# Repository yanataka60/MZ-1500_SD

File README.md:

# MZ-1500にSD-CARDからのアプリケーション起動、ロード、セーブ機能

MZ-1500でSD-CARDからのアプリケーション起動、BASICなどのアプリケーションからSD-CARDへのロード、セーブを実現するものです。

#### 2024.8.8 BASIC MZ-5Z001でSD対応パッチ更新しました。今のところ、LOAD、SAVEに問題は発生していません。
#### ~~2024.8.6 BASIC MZ-5Z001でSDからのLOAD実行した後に別プログラムをLOADしようとすると高確率で暴走してしまうようです。原因調査中ですので使用にはご注意ください。~~
#### 2024.8.5 BASIC MZ-5Z001でSDからのLOAD、SAVEに対応しました。
#### ~~MZ-1500でSD-CARDからのアプリケーション起動、BASICなどのアプリケーションからSD-CARDへのロード、セーブを実現するものですが、現在は標準BASIC MZ-5Z001もBASICプログラムのLOAD、SAVEに対応できていませんので機械語ゲームの起動等限定的な利用になります。~~

　MZ-1500にはMZ-1R12が装備されているとS-RAMに保存されているプログラムから起動する機能がありますが、疑似的にMZ-1R12のふりをすることでMZ-1500_SDに搭載したROMからSD-CARDからアプリケーションを起動させる機能を持たせたMONITORプログラムを起動させます。

　SD対応MONITORからはFD又はFDLコマンドでSDからアプリケーションをLOAD実行ができます。

　SD対応MONITORは本体ROMの1Z-009BをRAMにコピーしてうえでSD対応のプログラムを付加しています。

　LOAD実行範囲は、0000h～CFFFhです。アプリケーション、ゲームを起動させるにはほぼ問題ないと思います。

　ただし、多段ロード、QDソフトには対応していません。

　なお、アプリケーション中でのSD-CARDとのロード、セーブについては、MZ-80Kシリーズ、MZ-1200、MZ-700、MZ-1500のすべてのアプリケーションごとにSD-CARD対応化を行う必要があります。

　現在、アプリケーション中でのSD-CARDとのLOAD、SAVEに対応できているものは以下のとおりです。

|アプリケーション名|備考|
| ------------ | ------------ |
|BASIC MZ-5Z001||
|MZ-700用SBasic 1Z-007B||
|ROPOKO v1.2.2||
|ROPOKO体験版||
|ROPOKO80K v1.1.2||

　なお、Arduino、ROMへ書き込むための機器が別途必要となります。

### (2026.8.15追記)多段ロードに対応するためArduinoプログラム及び1Z-009B_SD_Launcher.binを更新しました。

### 多段ロードの詳細についてはMZ-80K_SDの「多段ロード対応」を参照してください。

　多段ロード対応:https://github.com/yanataka60/MZ80K_SD#%E5%A4%9A%E6%AE%B5%E3%83%AD%E3%83%BC%E3%83%89%E5%AF%BE%E5%BF%9C2026813

#### 　ただし、SDアクセスルーチンがROM上にあるMZ-80K_SD、MZ-700_SDとは違いMZ-1500_SDはRAM上にあるため、１段目のプログラムのロード範囲がC100h以降であるとSDアクセスルーチンを破壊してしまい、多段ロードが機能しません。

　ArduinoプログラムはMZ-80K_SD用に更新したものがそのまま使えます。

## 回路図
　KiCadフォルダ内のMZ-1500_SD.pdfを参照してください。

[回路図](https://github.com/yanataka60/MZ-1500_SD/blob/main/KiCad/MZ-1500_SD.pdf)

|番号|品名|数量|備考|
| ------------ | ------------ | ------------ | ------------ |
||J2、J3のいずれか|||
|J2|Micro_SD_Card_Kit|1|秋月電子通商 AE-microSD-LLCNV (注1)|
|J3|MicroSD Card Adapter|1|Arduino等に使われる5V電源に対応したもの(注3)|
|U1,U2|74LS04|2||
|U3,U4|74LS30|2||
|U5|74LS10|1||
|U6|74LS14|1||
|U7|8255|1||
|U8|Arduino_Pro_Mini_5V|1|Atmega328版を使用 168版は不可。(注2)|
|U9-U12|74LS193|4||
|U13|27256/29C256/27512/27C512相当品|1|27256/29C256を使うときは、S1を5V側にして使うこと。28C256はピン配置が違うので使えません。|
|U14|74LS245|1||
|C1,C2,C4-C14|積層セラミックコンデンサ 0.1uF|13||
|C3|電解コンデンサ 16v100uF|1||
|C15|積層セラミックコンデンサ 220pF|1||
|R1|カーボン抵抗 100Ω|1||
|S1|3Pスライドスイッチ|1|秋月電子通商 SS12D01G4など|
||ピンヘッダ|2Pin分|Arduino_Pro_MiniにはA4、A5用のピンヘッダが付いていないため別途調達が必要です 秋月電子通商 PH-1x40SGなど|
||ピンソケット(任意)|26Pin分|Arduino_Pro_Miniを取り外し可能としたい場合に調達します 秋月電子通商 FHU-1x42SGなど|

　　　注1)秋月電子通商　AE-microSD-LLCNVのJ1ジャンパはショートしてください。

　　　注2)Arduino Pro MiniはA4、A5ピンも使っています。

　　　注3)MicroSD Card Adapterを使う場合

　　　　　J3に取り付けます。

MicroSD Card Adapterについているピンヘッダを除去してハンダ付けするのが一番確実ですが、J3の穴にMicroSD Card Adapterをぴったりと押しつけ、裏から多めにハンダを流し込むことでハンダ付けをする方法もあります。なお、この方法の時にはしっかりハンダ付けが出来たかテスターで導通を確認しておいた方が安心です。

ハンダ付けに自信のない方はJ2の秋月電子通商　AE-microSD-LLCNVをお使いください。AE-microSD-LLCNVならパワーLED、アクセスLEDが付いています。

## ROMへの書込み
　Z80フォルダの「1Z-009B_Launcher」フォルダ内の1Z-009B_SD_Launcher.binをROMライター(TL866II Plus等)を使って27C256に書き込んでください。

　27C512を使えば二つのバイナリファイルを切り替えて使うような使い方ができます。このとき、一つのバイナリファイルは32KByte、二つ合わせて64KByteにして書き込んでください。

　もうひとつのLauncherとして「Oh!MZ別冊 ADVANCED MZ-700」に掲載されたMZ-80K/CコンパチモニタFN-700をベースとしたFN-700_1500SD_Launcherを作成しました。

### FN-700_1500SD_Launcher.bin作成手順
　1)「Oh!MZ別冊 ADVANCED MZ-700」掲載のMZ-80K/CコンパチモニタFN-700のMZTファイルを用意します。

　2)MZTファイルのヘッダ128Byte分は不要ですのでバイナリエディタで削除します。

　3)先頭の16Byteも不要ですので削除し、C3 4A 00から始まる4096Byteのファイルとします。

　4)以下のアドレスを修正します。

|ADDRESS|修正前|修正後|
| ------------ | ------------ | ------------ |
|0179|F0|C1|
|0437|D5 C5 E5|C3 04 C1|
|0476|D5 C5 E5|C3 07 C1|
|04D9|D5 C5 E5|C3 0A C1|
|04F9|D5 C5 E5|C3 0D C1|
|0589|D5 C5 E5|C3 10 C1|

　5)Z80フォルダの「FN-700_Launcher」フォルダ内のFN-700_1500SD.binを先程加工したFN-700の後ろに連結します。6430Byteのファイルになります。

　6)先頭に9Byteのヘッダ「00 00 00 12 00 22 00 00 00」を付加します。6439Byteのファイルになります。FN-700_1500SD_DATA.binなど適当なファイル名を付けて保存します。

　7)Z80フォルダの「FN-700_Launcher」フォルダ内の1Z-1R12_Header.exeを実行し、先程作成したFN-700_1500SD_DATA.binをドラッグ＆ドロップします。

　8)1Z-1R12_Header.exeを起動したフォルダにチェックサムを正しく計算したMZ1500SD.ROMが作成されます。6574Byteのファイルになっているはずです。

　9)MZ1500SD.ROM(FN-700_1500SD_Launcher.bin)をROMライター(TL866II Plus等)を使ってROMに書き込んでください。

　または、5)で出来たファイルに以下のヘッダを付けてMZTファイルとして保存すれば1Z-009B_Launcherから実行することもできます。

[0000] 01 46 4E 2D 37 30 30 20 31 35 30 30 53 44 0D 0D

[0010] 0D 0D 1E 19 00 12 00 22 00 00 00 00 00 00 00 00

[0020] 00 00 00 00 00 00 00 00 00 00 00 00 00 00 00 00

[0030] 00 00 00 00 00 00 00 00 00 00 00 00 00 00 00 00

[0040] 00 00 00 00 00 00 00 00 00 00 00 00 00 00 00 00

[0050] 00 00 00 00 00 00 00 00 00 00 00 00 00 00 00 00

[0060] 00 00 00 00 00 00 00 00 00 00 00 00 00 00 00 00

[0070] 00 00 00 00 00 00 00 00 00 00 00 00 00 00 00 00

## Arduinoプログラム

　MZ-80K_SDと全く同じものを使用しています。

https://github.com/yanataka60/MZ80K_SD/tree/main/Arduino/MZ-80K_SD

　MZ-80K_SDでソケットを使用して差込式にしているのであればそのままMZ-1500_SDに差して使えます。

　Arduino IDEを使ってMZ-80Kリポジトリ Arduinoフォルダ内のMZ-80K_SD.inoを書き込みます。

　SdFatライブラリを使用しているのでArduino IDEメニューのライブラリの管理からライブラリマネージャを立ち上げて「SdFat」をインストールしてください。

　「SdFat」で検索すれば見つかります。「SdFat」と「SdFat - Adafruit Fork」が見つかりますが「SdFat」のほうを使っています。

注)Arduinoを基板に直付けしている場合、Arduinoプログラムを書き込むときは、MZ-15000本体とは接続を外し、74LS04を外したうえで書き込んでください。

## 接続
　拡張スロットに差し込んで使います。

　なお、拡張スロットから引き抜くときに引き抜きやすいよう基板両サイドと中央に穴を開けてあります。

　穴にドライバー等を引っ掛けて押し出すようにすれば引き抜きやすいと思います。

## SD-CARD
　出来れば8GB以下のSDカードを用意してください。

　ArduinoのSdFatライブラリは、SD規格(最大2GB)、SDHC規格(2GB～32GB)に対応していますが、SDXC規格(32GB～2TB)には対応していません。

　また、SDHC規格のSDカードであっても32GB、16GBは相性により動作しないものがあるようです。

　FAT16又はFAT32が認識できます。NTFSは認識できません。

　ルートに置かれたMZTファイルのみ認識できます。(MZT以外のファイル、フォルダも表示されますがLOAD実行の対象になりません)

　ファイル名は「.MZT」を除いて32文字まで、ただし半角カタカナ、及び一部の記号はArduinoが認識しないので使えません。パソコンでファイル名を付けるときはアルファベット、数字および空白でファイル名をつけてください。

## 操作方法
　ROM起動させた場合にMONITORコマンド入力待ちから以下のコマンドが拡張されます。

　以下、SD-CARD内のファイルに付けられるファイル名をDOSファイル名、MZT形式ファイルのインフォメーションブロック内ファイル名をIBFファイル名とします。

### FD[CR]
　FDのみでDOSファイル名「0000.MZT」がLOAD及び実行されます。

　「0000.MZT」は、パソコンでBASIC等をリネームコピーして作成してください。

　LOAD実行可能範囲は0000h～CFFFhです。

### FD　DOSファイル名[CR]
　DOSファイル名で指定したバイナリファイルをLOADして実行します。

　「.MZT」は省略可能です。

　LOAD実行可能範囲は0000h～CFFFhです。

例)

FD　TEST[CR]

### FDL[CR]
　SD-CARDルートディレクトリにあるファイルの一覧を表示します。20件表示したところで指示待ちになるので打ち切るならSHIFT+BREAK又は↑を入力すると打ち切られ、Bキーで前の20件に戻ります。それ以外のキーで次の20件を表示します。

　行頭に「*FD」を付加して表示してあるので実行したいファイルにカーソルキーを合わせて[CR]キーを押すだけでLOAD、実行が可能です。

　表示される順番は、登録順となりファイル名アルファベッド順などのソートした順で表示することはできません。

　LOAD実行可能範囲は0000h～CFFFhです。

### FDL　x[CR]
ファイル名がxで始まるファイルの一覧を表示します。20件表示したところで指示待ちになるので打ち切るならSHIFT+BREAK又は↑を入力すると打ち切られ、Bキーで前の20件に戻ります。それ以外のキーで次の20件を表示します。

xはMZのキーボードから入力可能な32文字までの文字列です。(数字、記号、アルファベット)

　LOAD実行可能範囲は0000h～CFFFhです。

例)

FDL S[CR]

FDL SP[CR]

FDL BASIC S[CR]

### FDA　DOSファイル名[CR]
　DOSファイル名で指定したファイルを「0000.MZT」という名前でリネームコピーします。

　FDLコマンドで表示されたファイル名をカーソルで選択し、行頭の「*FD」に「A」だけ付加して[CR]キーを押せば簡単です。

### FDS　SAVE開始アドレス　SAVE終了アドレス　実行開始アドレス　DOSファイル名[CR]
　SAVE開始アドレスからSAVE終了アドレスまでをDOSファイル名でSAVEします。

　SAVE開始アドレス、SAVE終了アドレス、実行開始アドレスは16進数4桁で指定します。DOSファイル名の「.MZT」は省略可能です。

例)

FDS　1200　2FFF　1200　TEST[CR]

### FDC　DOSファイル名[CR]
　DOSファイル名で指定したファイルをコピーします。

　FDLコマンドで表示されたファイル名をカーソルで選択し、行頭の「*FD」に「C」だけ付加して[CR]キーを押せば簡単です。

　DOSファイル名を入力し、[CR]キーを押すと「NEW NAME:」と聞いてくるので新しいDOSファイル名を入力して[CR]キーを押します。

　新しいDOSファイル名に既にあるDOSファイル名を指定するとコピーせずに中断します。

例)

FDC　TEST[CR]

NEW NAME:TEST2[CR]

### FDR　DOSファイル名[CR]
　DOSファイル名で指定したファイルをリネームします。

　FDLコマンドで表示されたファイル名をカーソルで選択し、行頭の「*FD」に「R」だけ付加して[CR]キーを押せば簡単です。

　DOSファイル名を入力し、[CR]キーを押すと「NEW NAME:」と聞いてくるので新しいDOSファイル名を入力して[CR]キーを押します。

　新しいDOSファイル名に既にあるDOSファイル名を指定するとリネームせずに中断します。

例)

FDR　TEST[CR]

NEW NAME:TEST2[CR]

### FDD　DOSファイル名[CR]
　DOSファイル名で指定したファイルを削除します。

　FDLコマンドで表示されたファイル名をカーソルで選択し、行頭の「*FD」に「D」だけ付加して[CR]キーを押せば簡単です。

　DOSファイル名を入力し、[CR]キーを押すと「FILE DELETE?(Y:OK ELSE:CANSEL)」と聞いてくるのでYを押せば削除されます。Y以外のキーを押すとキャンセルとなります。

### FDP　DOSファイル名[CR]
　DOSファイル名で指定したファイルの内容をDUMPします。

　FDLコマンドで表示されたファイル名をカーソルで選択し、行頭の「*FD」に「P」だけ付加して[CR]キーを押せば簡単です。

　DOSファイル名を入力し、[CR]キーを押すとファイルの内容を128Byteを一画面として表示します。

　一画面表示したところで「NEXT:ANY BACK:B BREAK:SHIFT+BREAK」と表示して指示待ちとなるのでBで前の128Byteを表示、SHIFT+BREAKで中止、それ以外のキーで次の128Byteの表示となります。

　ファイルサイズが128Byteで割り切れない場合には最後のページは128Byteに揃うまで00Hで埋められます。

　ファイル内容を書き換えることはできません。

### FDM　開始アドレス[CR]
　開始アドレスからMZ-80Kのメモリ内容を128Byteを一画面として表示します。

　一画面表示したところで「NEXT:ANY BACK:B BREAK:SHIFT+BREAK」と表示して指示待ちとなるのでBで前の128Byteを表示、SHIFT+BREAKで中止、それ以外のキーで次の128Byteの表示となります。

　一画面表示している途中でもSHIFT+BREAKでいつでも中止できます。

### FDW　開始アドレス　1Byte(16進2桁)データ[CR]
　開始アドレスから16進2桁データをMZ-80Kのメモリに書き込みます。

　開始アドレスに続けて16進2桁で書き込むデータを記述し[CR]キーを押します。データの区切りの空白は無視しますのであってもなくても構いません。

　16進2桁のByteデータは一行に収まる範囲なら何Byte分を続けても構いません。

　一行入力して[CR]キーを押すとデータが書き込まれ、次のアドレスが表示されるので続けてデータを入力していけます。

　また、アドレスを修正すれば戻って修正や離れたアドレスにデータを書き込むことも可能です。

　データの書き込みを止めるときは表示されたアドレスにデータを書かずに[CR]キーを押します。

　16進数以外を入力して[CR]キーを押した場合には16進数以外を入力した直前までの有効なデータを書き込み次のアドレスを表示します。

例)

*FDW　1200　01　02　03　04　05　06　07　08[CR]

*FDW　1200　0102030405060708[CR]

*FDW　1200[CR]　(止めるとき)

*FDW　1200　12　34　5/[CR]　(12　34まで書き込まれます)

## アプリケーションからのLOAD、SAVE
　MZ-1500はE800h～FFFFhにROMが置かれており、MZ-80Kシリーズ、MZ-1200、MZ-700のように特定のアドレス(F000h等)にSDアクセスルーチンを格納したROMを置くことが出来ないため、SDへのLOAD、SAVEはアプリケーション個々にSDアクセスルーチンをどこに置くか検討が必要になります。

　また、文字列入力等モニタルーチンを使っている箇所があるのでSP-1002、MZ-1Z009Bではない独自MONITOR上で動くアプリケーションはMONITORの解析も必要です。

　「Oh!MZ別冊 ADVANCED MZ-700」に掲載されたMZ-80K/CコンパチモニタFN-700を使えばMZ-80K_SDに対応したMZ-80K用アプリケーションのほとんどがMZ-700+MZ-80K_SDでは使えましたが、MZ-1500+MZ-1500_SDでは起動は出来ますが、アプリケーション内でのLOAD、SAVEはそのままでは使えません。

### MZ-1500用BASIC MZ-5Z001

##### 2024.8.10 LOAD時の特殊コマンド「*FDL」を使えるようにしました。これによりLOADコマンドの使い方が若干変わっています。
　MZ-5Z001をイメージ化したmztファイルが必要です。

　MZ-5Z001のイメージ化については簡単に書きますので詳細はWebで検索ください。

　kitahei88氏が開発、頒布されているQDC又はNorixさんが開発されたVirtuaQDでQDFファイルに変換、TAKEDAさんのEmuZ-1500を起動し、モニタからQCコマンドでQDFファイル中のMZ-5Z001を読み込ませた後、空のmztファイルをQDドライブにインサートしてYを押すと出来上がります。

　MZ-5Z001.mztをバイナリエディタで開きます。ファイルの最後はA295hですが、A29Fhまで00hで埋めます。(もしかしたらバージョン違いでA295hではないかもしれませんが、A29Fhまで00hで埋められれば大丈夫だと思います。)

　Z80フォルダ中MZ-5Z001フォルダにある「mz-5z001_BOOT.bin」をMZ-5Z001.mztの後ろ(A2A0h～)に付加します。ファイルサイズ42581Byteになります。

　MZ-5Z001.mztのヘッダを修正し、ファイルサイズをA5D5h、実行アドレスをA220hとします。

　パッチを当てたファイルを「BASIC 1Z-5Z001-SD.MZT」等パッチを当てたことが識別できるファイル名で保存してお使いください。

#### AUTO RUNへの対応
　なぜか、AUTO RUNが自動実行されないのでAUTO RUNが自動実行されるパッチを別に作成しました。適宜使い分けてください。

　MZ-5Z001.mztをバイナリエディタで開き、A29Fhまで00hで埋めるところまでは同じです。

　Z80フォルダ中MZ-5Z001フォルダにある「mz-5z001_BOOT_AUTORUN.bin」をMZ-5Z001.mztの後ろ(A2A0h～)に付加します。ファイルサイズ42592Byteになります。

　MZ-5Z001.mztのヘッダを修正し、ファイルサイズをA5E0h、実行アドレスをA220hとします。

　パッチを当てたファイルを「BASIC 1Z-5Z001-SD-AUTORUN.MZT」等パッチを当てたことが識別できるファイル名で保存してお使いください。

　MZ-5Z001が起動したときにSDカードに保存されている「AUTO RUN.MZT」が自動実行されます。ファイルモードは「05」である必要があります。「05」以外のファイルモードになっていると「CMT:Illegal Filemode error」と表示されます。

　「AUTO RUN.MZT」が見つからない場合は、「CMT:Check sum error」と表示されます。

#### 注意点
　BASIC MZ-5Z001の解析資料が乏しい中で一応SDに対応してみましたが、不具合が残っている可能性があることをご了承願います。

　パッチによりデフォルトメディアをQDからCMTに変更してあります。SDからLOAD、SAVEを行うときに機械名「CMT:」の指定の必要はありません。

　SDアクセスルーチンをFDディレクトリバッファに置いていますのでFDと両立は出来ません。

　QD用のBASICプログラムをSDから読込もうとすると「CMT:Illegal Filemode error」と表示され読み込めません。

　同じMZ-5Z001のBASICプログラムであってもCMT用のファイルモードは「05」、QD用のファイルモードは「02」と異なっています。

　バイナリエディタで先頭の1Byteを「02」から「05」に修正すればCMT用となり、SDから読込めるようになります。

##### 2024.8.18 LOAD"xxxx",A、SAVE"xxxx",A、RUN"xxxx",Aのアスキー形式でのLOAD、SAVEも正常に動作するようになりました。
##### ~~LOAD"xxxx",A、SAVE"xxxx",A、RUN"xxxx",Aのアスキー形式でのLOAD、SAVEの実行は出来ません。実行すると暴走するので実行しないでください。~~

　RUN"xxxx"及びRUN"xxxx",RコマンドでSDから読込後即実行は可能です。

#### ファイル名について

　オリジナル通りに16文字までがファイル名となりますが、半角カナ文字はArduinoが認識できない、一部の記号はMZ-1500のキーボードから入力できないので使えません。

　ロングファイルネームに対応できなかった引き換えにLOADコマンドもオリジナル通りの入力方法となり、そのままDOSファイル名となります。

　LOADコマンドを実行したときに「CMT:Check sum error」と表示された場合は、16文字以上のファイル名が付けられているか、指定したファイル名のファイルがSDに存在しないかのどちらかかです。ファイルを確認してください。

例)

　SAVE "TEST.BAS" : TEST.BAS.MZTというDOSファイル名で保存されます。

　SAVE "TEST"     : TEST.MZTというDOSファイル名で保存されます。

　LOAD "TEST.BAS" : TEST.BAS.MZTというDOSファイル名のファイルがロードされます。

　LOAD "TEST"     : TEST.MZTというDOSファイル名のファイルがロードされます。

　DOSファイル名が「TEST SBASIC EIGHT.MZT」の場合、LOAD "TEST SBASIC EIGHT"と入力しても「TEST SBASIC EIGH.MZT」というDOSファイルを探しに行くためロードできません。

#### LOAD時の特殊コマンド
　LOADに続けてファイル名を指定した場合は今まで通り指定したファイル名のプログラムがSDから読み込まれますが、ファイル名を指定せずにLOADだけで実行した場合は、「DOS FILE:」と表示して行入力待ちになります。

　このとき入力できるDOSファイル名は「.MZT」を除いて32文字までとなります。

　ただし半角カタカナ、及び一部の記号はArduinoが認識しないので使えません。パソコンでファイル名を付けるときはアルファベット、数字および空白でファイル名をつけてください。

　またファイル名以外に以下の特殊コマンドが使用可能となります。

##### *FDL[CR]
##### *FDL x[CR]
　MONITORコマンド入力待ちからのFDL、FDL xと全く同等のファイル一覧機能が使えます。

　検索結果の行頭には「DOS FILE:」を付加して表示してあるのでLOADしたいファイルにカーソルキーを合わせて[CR]キーを押すだけでLOADが可能です。

### MZ-700用S-BASIC 1Z-007B
　Z80フォルダ中SBASIC PATCHフォルダにあるSBASIC_patch1.bin、SBASIC_patch2.binの二つをS-BASICのMZTファイルに当てます。

　MZTファイルの00A1Hから00AFHまで(実アドレス0021H～002FH)をSBASIC_patch1.binと差し替えます。

　MZTファイルの2E80Hから2FE3Hまで(実アドレス2E00H～2F63H)をSBASIC_patch2.binと差し替えます。

　パッチを当てたファイルを「S-BASIC 1Z-007B 1500SD.MZT」等パッチを当てたことが識別できるファイル名で保存してお使いください。

#### ファイル名について

　オリジナル通りに16文字までがファイル名となりますが、半角カナ文字はArduinoが認識できない、一部の記号はMZ-1500のキーボードから入力できないので使えません。

　ロングファイルネームに対応できなかった引き換えにLOADコマンドもオリジナル通りの入力方法となり、そのままDOSファイル名となります。

例)

　SAVE "TEST.BAS" : TEST.BAS.MZTというDOSファイル名で保存されます。

　SAVE "TEST"     : TEST.MZTというDOSファイル名で保存されます。

　LOAD "TEST.BAS" : TEST.BAS.MZTというDOSファイル名のファイルがロードされます。

　LOAD "TEST"     : TEST.MZTというDOSファイル名のファイルがロードされます。

　DOSファイル名が「TEST SBASIC EIGHT.MZT」の場合、LOAD "TEST SBASIC EIGHT"と入力しても「TEST SBASIC EIGH.MZT」というDOSファイルを探しに行くためロードできません。

### MZ-700版ロポコのMZ-1500_SD対応パッチ
　この度、作者のTookato様がロポコVersion 1.2.2をリリースされましたが、このアーカイブには無圧縮版のロポコが同梱されており、パッチを当てることでMZ-1500_SD対応とすることが出来ましたので公開します。

#### 使い方
　ロポコVersion 1.2.2を入手します。

　解凍すると「Uncompressed」フォルダにROPOKO-PR.MZT、ROPOKO-AR.MZT、ROPOKO-BR.MZT、の三つのファイルがあるのでSDカードにコピーします。

　このGitHubのMZ80K_SDリポジトリ中の「ROPOKO」フォルダ内の「ROPOKO-SD.MZT」をSDカードにコピーします。

##### 「ROPOKO-SD.MZT」はMZ-80K_SD用と共用です。
https://github.com/yanataka60/MZ80K_SD/tree/main/ROPOKO

　FDL又はFDコマンドを使ってSDカードにコピーした「ROPOKO-SD.MZT」を実行します。

　ROPOKO-PR.MZTを自動的に読込み、SD対応のパッチを当て、ロポコが起動します。

　シナリオの読込は、例えばシナリオAを選択し、「テープをセットしてください」と表示された後にCRを一回押すと「DOS FILE:」と表示されるので「ROPOKO-AR」と正しく入力し、CRを押すことで読み込みが始まります。

　データのセーブ・ロードはF3キーを押し、S:Save L:Loadを選択するとファイル名の入力になります。A面では「SA-」B面では「SB-」で始まるファイル名とし「SA-1/2/3...」のように異なる名前を付けるところはオリジナルと同様です。

　ただし、セーブ時に既にあるファイル名を指定すると上書きしますのでお気を付けください。

### ロポコ(体験版)のMZ-1500_SD対応パッチ
　MZ-700版ロポコと同様にロポコ(体験版)もパッチを作成しました。

#### 使い方
　ロポコ(体験版)を入手します。

　解凍すると「Uncompressed」フォルダにROPOKO-TR.mztがあるのでSDカードにコピーします。

　このGitHubのMZ80K_SDリポジトリ中の「ROPOKO-TRIAL」フォルダ内の「ROPOKO-T-SD.MZT」をSDカードにコピーします。

##### 「ROPOKO-T-SD.MZT」はMZ-80K_SD用と共用です。
https://github.com/yanataka60/MZ80K_SD/tree/main/ROPOKO-TRIAL

　FDL又はFDコマンドを使ってSDカードにコピーした「ROPOKO-T-SD.MZT」を実行します。

　ROPOKO-TR.mztを自動的に読込み、SD対応のパッチを当て、ロポコ(体験版)が起動します。

　データのセーブ・ロードはF3キーを押し、S:Save L:Loadを選択するとファイル名の入力になります。A面では「SA-」B面では「SB-」で始まるファイル名とし「SA-1/2/3...」のように異なる名前を付けるところはオリジナルと同様です。

　ただし、セーブ時に既にあるファイル名を指定すると上書きしますのでお気を付けください。

### ロポコ for MZ-80K v1.1.2のMZ-1500_SD対応パッチ
　MZ-700版ロポコと同様にロポコ for MZ-80K v1.1.2もパッチを作成しました。

#### 使い方
　ロポコ for MZ-80K v1.1.2を入手します。

　解凍すると「Uncompressed」フォルダにROPOKO80K-PR.mztがあるのでSDカードにコピーします。

##### 注)ロポコ for MZ-80K v1.1.1以前のアーカイブにも非圧縮版のROPOKO80K-PR.mztが含まれていますが、対応していません。v1.1.2を入手してください。

　このGitHubのMZ-1500_SDリポジトリ中の「ROPOKO80K」フォルダ内の「ROPOKO80K-MZ1500SD.MZT」をSDカードにコピーします。

　FDL又はFDコマンドを使ってSDカードにコピーした「ROPOKO80K-MZ1500SD.MZT」を実行します。

　ROPOKO80K-PR.mztを自動的に読込み、SD対応のパッチを当て、ロポコ for MZ-80K v1.1.2が起動します。

　機種選択「6:MZ-700(SDカード)」を選択してください。MZ-1500+MZ-1500_SDで動作するようパッチを当てています。

　データのセーブ・ロードはF3キーを押し、S:Save L:Loadを選択するとファイル名の入力になります。A面では「SA-」B面では「SB-」C面では「SC-」で始まるファイル名とし「SA-1/2/3...」のように異なる名前を付けるところはオリジナルと同様です。

　ただし、セーブ時に既にあるファイル名を指定すると上書きしますのでお気を付けください。

### 汎用SDアクセスルーチン
　MZ-80Kシリーズ、MZ-1200、MZ-700、MZ-1500用アプリケーションへのMZ-1500_SDアクセスルーチンの組み込み及び自作アプリケーションのMZ-1500_SD対応用としてSDアクセスルーチンを抜き出しました。

　SP-1002、MZ-1Z009B、FN-700モニタの使用を前提としていますので独自モニタではサブルーチンコール及びワークエリアを修正する必要があります。

#### 使用法
　Z80フォルダ中「built-in SD ACCESS」フォルダのFD_rom1500.sのORGを適宜修正して使ってください。

　ソース中でORGはCD00hで定義されています。

　なおMZ-1500のバンク切替の仕様により、ORGをCD54h以降にすると正常動作できません。

|エントリポイント|名前|用途|
| -------------- | -- | -- |
|ORG+03h|MSHED|Write Infomation|

　Monitor 0436h CMT Write Infomation処理代替

　0436hをコール又はジャンプしている処理と差し替えてください。

　ファイル名、Save開始アドレス、Saveサイズ等の情報はIFBの情報を使います。

|エントリポイント|名前|用途|
| -------------- | -- | -- |
|ORG+06h|MSDAT|Write Data|

　Monitor 0475h CMT Write Data処理代替

　0475hをコール又はジャンプしている処理と差し替えてください。

|エントリポイント|名前|用途|
| -------------- | -- | -- |
|ORG+09h|MLHED|Read Infomation|

　Monitor 04D8h CMT Read Infomation処理代替

　04D8hをコール又はジャンプしている処理と差し替えてください。

　コール後に「DOS FILE:」と入力待ちになるのでSDから読み込みたいファイル名を指定します。

|エントリポイント|名前|用途|
| -------------- | -- | -- |
|ORG+0Ch|MLDAT|Read Data|

　Monitor 04F8h CMT Read Data処理代替

　04F8hをコール又はジャンプしている処理と差し替えてください。

|エントリポイント|名前|用途|
| -------------- | -- | -- |
|ORG+0Fh|MVRFY|Verify|

　Monitor 0588h CMT Verify処理代替

　0588hをコール又はジャンプしている処理と差し替えてください。

|エントリポイント|名前|用途|
| -------------- | -- | -- |
|ORG+12h|MSHED2|Write Infomation2|

　Monitor 0436h CMT Write Infomation処理代替(ファイル名指定可)

　0436hをコール又はジャンプしている処理と差し替えてください。

　MSHEDと同様ですが、コール後に「SAVE NAME:」と入力待ちになるのでSDへ保存するファイル名を指定することが出来ます。

|エントリポイント|名前|用途|
| -------------- | -- | -- |
|ORG+15h|MLHED2|Read Infomation2|

　Monitor 04D8h CMT Write Infomation処理代替

　04D8hをコール又はジャンプしている処理と差し替えてください。

　MLHEDと同様ですが、SDから読み込むファイル名をプログラム中から指定しておくことが出来ます。

　読み込むファイル名のアドレスDEレジスタにセットしてからコールしてください。なお、ファイル名の最後には0Dhが必要です。

### 1Z-1R12用ヘッダ作成プログラム
　FN-700_1500SD_Launcher.bin作成ツールとして「FN-700_Launcher」フォルダ内に用意した1Z-1R12_Header.exeですが、他のアプリケーションをMZ-1500_SDのROMから起動したい場合には以下のようにして書き込み用データを作成してください。

#### 1)アセンブラで作成したバイナリファイルから作成
　アセンブラで作成したバイナリファイルの先頭に9Byteのヘッダを付加します。

|オフセット|内容|セットする値|備考|
| ------------ | ------------ | ------------ | ------------ |
|+0|プログラム格納サイズ(L)|00|自動計算|
|+1|プログラム格納サイズ(H)|00|自動計算|
|+2|ロードアドレス (L)|ロードアドレス (L)||
|+3|ロードアドレス (H)|ロードアドレス (H)||
|+4|実行アドレス (L)|実行アドレス (L)||
|+5|実行アドレス (H)|実行アドレス (H)||
|+6|データ部チェックサム (L)|00|自動計算|
|+7|データ部チェックサム (H)|00|自動計算|
|+8|ヘッダ部チェックサム|00|自動計算|

　1Z-1R12_Header.exeを起動して9Byteを付加したバイナリファイルをドラッグ＆ドロップします。

　1Z-1R12_Header.exeを起動したフォルダにチェックサムを正しく計算したMZ1500SD.ROMというファイル名で作成されます。

#### 2)MZTファイルから作成
　1Z-1R12_Header.exeを起動してMZTファイルをドラッグ＆ドロップします。

　1Z-1R12_Header.exeを起動したフォルダにチェックサムを正しく計算したMZ1500SD.ROMというファイル名で作成されます。

## EMMボード for MZ-700からの起動
　拙作EMMボード for MZ-700をバッテリーバックアップに対応させたのでEMM_for_MZ-700から起動するコマンドを追加してみました。

　https://github.com/yanataka60/EMM_for_MZ-700

　コマンド「FDE0」～「FDE3」を使うことで「EMM0」～「EMM3」のHuBASICから起動させることが出来ます。

　なお、EMMの00000番地が「01h」でなければEMMからの起動はせずにコマンド待ちに戻りますが、00000番地以降に異常があってもチェックはしていないので最悪暴走します。

　MZ-1500用HuBASIC、MZ-80K用HuBASICではEMMがサポートされていません。EMMが使えるのはMZ-700用HuBASICのみとなりますが、テープ版しかなくそのままではEMMにHuBASICの起動イメージを作成することが出来ません。

　BouKiCHiさんのHuDiskなどを使いMZ-700用HuBASICの起動ディスクイメージを作成したうえでEMMMENUのEMMLOADでEMMに書き込む必要があります。

### BOOT LOADERをROMに書き込む
　(2026.8.15)多段ロード対応に伴い、MZ-1500_SD/Z80/1Z-009B_Launcher/1Z-009B_SD_Launcher.binに統合しました。

~~EMMフォルダ内の1Z-009B_SD_Launcher.binをROMライター(TL866II Plus等)を使って27256に書き込んでください。~~

## 謝辞
　基板の作成に当たり以下のデータを使わせていただきました。ありがとうございました。

　Arduino Pro Mini

　　https://github.com/g200kg/kicad-lib-arduino

　AE-microSD-LLCNV

　　https://github.com/kuninet/PC-8001-SD-8kRAM

## 追記
2024.8.4 BASIC MZ-5Z001のSD対応パッチを公開しました。

2024.8.5 BASIC MZ-5Z001のSD対応パッチ修正版を公開しました。

　　　　BASIC MZ-5Z001のAUTORUN対応SDパッチを公開しました。

2024.8.6 BASIC MZ-5Z001のSD対応パッチ修正版にも不具合があるので調査中です。現在判っている範囲で修正。

　　　　　　LOADし実行までは問題ないが、別プログラムをLOADしようとすると固まってしまう。短いプログラム同士だと発生しないが、長いプログラムのLOAD実行後に発生するよう。

2024.8.8 BASIC MZ-5Z001のSD対応パッチを更新しました。

2024.8.10 BASIC MZ-5Z001のLOADコマンドで「*FDL」を使えるようにした。

2024.8.18 ecd102様に教えて頂いた情報に基づいてmz-5z001_SD_ACCRESSを修正。

2025.12.4 kuran_kuranさんにArduinoプログラムのバグを発見していただきました。精査した結果、不要な処理が含まれていることが原因であったため不要な処理部分を削除しました。なお、未修正のままでも実害はありません。kuran_kuranさん、ありがとうございました。

2026.1.23 EMMサポートプログラムを追加。

2026.3.1 MZ-1500_SDリポジトリEMMフォルダ内の1Z-009B_SD_Launcher.binがCHECKSUM計算前のファイルをアップしており、正常起動できませんでしたので更新しました。

2026.8.15 多段ロードに対応しました。

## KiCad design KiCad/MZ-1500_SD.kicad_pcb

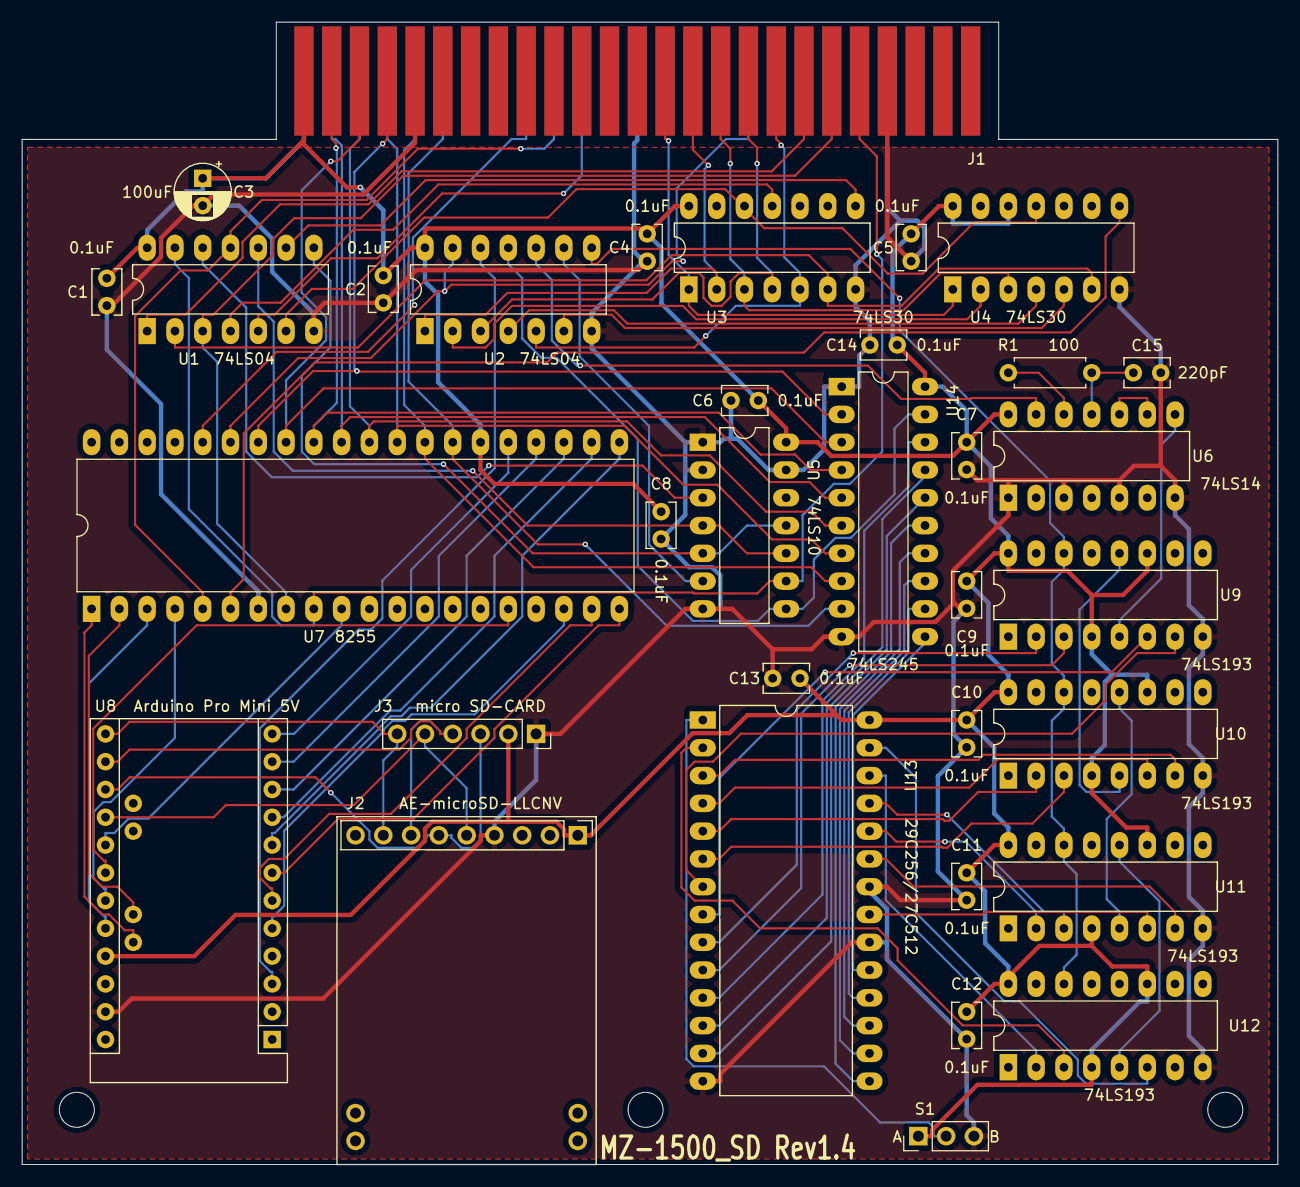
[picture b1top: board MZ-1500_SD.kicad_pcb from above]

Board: 2 copper layers, 114.8 x 104.4 mm, 37 parts (0 on the bottom side), 87 nets.

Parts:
C1, C2, C4, C5, C6, C7, C8, C9, C10, C11, C12, C13, C14: 0.1uF; C_Rect_L4.0mm_W2.5mm_P2.50mm
C3: 100uF; CP_Radial_D5.0mm_P2.50mm
C15: 220pF; C_Rect_L4.0mm_W2.5mm_P2.50mm
J1: MZ-1500 BUS; BUS_50Pin
J2: Micro_SD_Card_Kit; AE-microSD-LLCNV
J3: MicroSD Card Adapter; PinSocket_1x06_P2.54mm_Vertical
MH1, MH2, MH3: MountingHole_3.2mm_M3
R1: 100; R_Axial_DIN0207_L6.3mm_D2.5mm_P7.62mm_Horizontal
S1: A_B_CHANGE; PinHeader_1x03_P2.54mm_Vertical
U1, U2: 74LS04; DIP-14_W7.62mm_LongPads
U3, U4: 74LS30; DIP-14_W7.62mm_LongPads
U5: 74LS10; DIP-14_W7.62mm_LongPads
U6: 74LS14; DIP-14_W7.62mm_LongPads
U7: 8255; DIP-40_W15.24mm_LongPads
U8: Arduino_Pro_Mini
U9, U10, U11, U12: 74LS193; DIP-16_W7.62mm_LongPads
U13: 29C256/27C512; DIP-28_W15.24mm_LongPads
U14: 74LS245; DIP-20_W7.62mm_LongPads

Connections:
+5V: C1.1, C2.1, C3.1, C4.1, C5.1, C6.1, C7.1, C8.1, C9.1, C10.1, C11.1, C12.1, C13.1, C14.1, J1.1, J1.2, J2.1, J3.2, S1.1, U1.14, U2.14, U3.14, U4.12, U4.14, U5.14, U6.14, U7.26, U8.21, U9.4, U9.11, U9.16, U10.4, U10.11, U10.16, U11.4, U11.11, U11.16, U12.4, U12.11, U12.16, U13.28, U14.20
/A0: J1.42, U1.13, U5.9, U7.9
/A1: J1.40, U1.3, U7.8
/A2: J1.38, U1.1
/A3: J1.36, U2.5, U3.5
/A4: J1.34, U2.3, U3.4
/A5: J1.32, U3.3, U4.3
/A6: J1.30, U2.1, U3.2
/A7: J1.28, U3.1, U4.1
/CS: J2.8, J3.6, U8.13
/D0: J1.8, U7.34, U14.2
/D1: J1.6, U7.33, U14.3
/D2: J1.4, U7.32, U14.4
/D3: J1.3, U7.31, U14.5
/D4: J1.5, U7.30, U14.6
/D5: J1.7, U7.29, U14.7
/D6: J1.9, U7.28, U14.8
/D7: J1.11, U7.27, U14.9
/MISO: J2.6, J3.3, U8.15
/MOSI: J2.7, J3.4, U8.14
/RESET: J1.33, U2.13, U7.35
/SCK: J2.5, J3.5, U8.16
/~IORQ: J1.21, U1.5
/~RD: J1.19, U1.11, U7.5
/~WR: J1.17, U7.36
GND: C1.2, C2.2, C3.2, C4.2, C5.2, C6.2, C7.2, C8.2, C9.2, C10.2, C11.2, C12.2, C13.2, C14.2, C15.2, J1.10, J1.25, J1.43, J1.44, J2.4, J3.1, S1.3, U1.7, U2.7, U3.7, U4.7, U5.1, U5.2, U5.7, U5.13, U6.1, U6.3, U6.5, U6.7, U7.7, U8.23, U9.8, U10.8, U11.8, U12.8, U13.14, U13.20, U13.22, U14.1, U14.10
unnamed: C15.1, R1.2, U6.11
unnamed: R1.1, U6.12
unnamed: S1.2, U13.1
unnamed: U1.2, U3.6, U4.6
unnamed: U1.4, U3.11
unnamed: U1.6, U3.12, U4.11
unnamed: U1.8, U5.5, U5.11
unnamed: U1.9, U3.8
unnamed: U1.10, U5.4, U5.10
unnamed: U1.12, U5.3
unnamed: U2.2, U4.2
unnamed: U2.4, U4.4
unnamed: U2.6, U4.5
unnamed: U2.9, U5.6
unnamed: U2.10, U6.13
unnamed: U2.12, U8.3
unnamed: U4.8, U7.6
unnamed: U6.8, U9.5
unnamed: U6.9, U6.10
unnamed: U7.1, U8.A5
unnamed: U7.2, U8.A4
unnamed: U7.3, U8.20
unnamed: U7.4, U8.19
unnamed: U7.10, U8.17
unnamed: U7.16, U8.18
unnamed: U7.18, U8.5
unnamed: U7.19, U8.6
unnamed: U7.20, U8.7
unnamed: U7.21, U8.8
unnamed: U7.22, U8.9
unnamed: U7.23, U8.10
unnamed: U7.24, U8.11
unnamed: U7.25, U8.12
unnamed: U10.2, U13.5
unnamed: U10.3, U13.6
unnamed: U9.12, U10.5
unnamed: U10.6, U13.4
unnamed: U10.7, U13.3
unnamed: U10.12, U11.5
unnamed: U2.8, U9.14, U10.14, U11.14, U12.14
unnamed: U11.2, U13.24
unnamed: U11.3, U13.25
unnamed: U11.6, U13.21
unnamed: U11.7, U13.23
unnamed: U11.12, U12.5
unnamed: U12.2, U13.26
unnamed: U12.3, U13.2
unnamed: U12.6, U13.27
unnamed: U9.7, U13.7
unnamed: U9.6, U13.8
unnamed: U9.2, U13.9
unnamed: U9.3, U13.10
unnamed: U13.11, U14.18
unnamed: U13.12, U14.17
unnamed: U13.13, U14.16
unnamed: U13.15, U14.15
unnamed: U13.16, U14.14
unnamed: U13.17, U14.13
unnamed: U13.18, U14.12
unnamed: U13.19, U14.11
unnamed: U2.11, U5.8, U14.19
